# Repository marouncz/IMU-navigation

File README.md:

# IMU-navigation
This is a repository for my bachelor's thesis regarding IMU navigation

# Probrat 13.12.2023
+ mám v pohodě citaci datasheetu?

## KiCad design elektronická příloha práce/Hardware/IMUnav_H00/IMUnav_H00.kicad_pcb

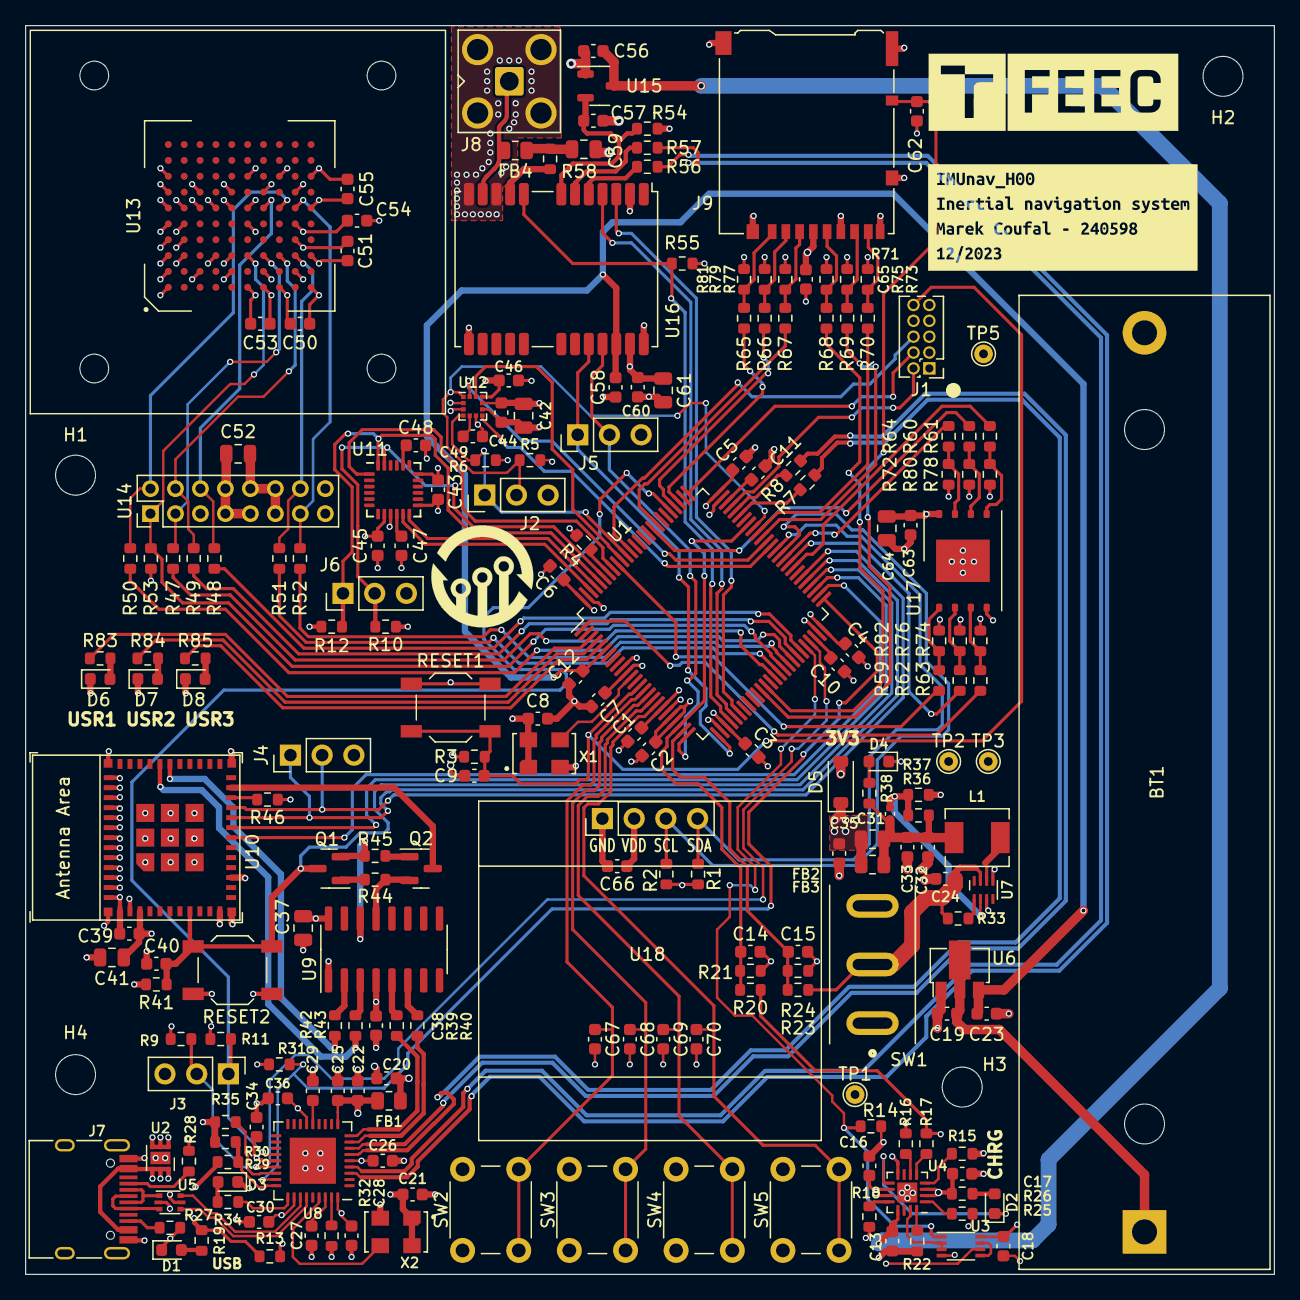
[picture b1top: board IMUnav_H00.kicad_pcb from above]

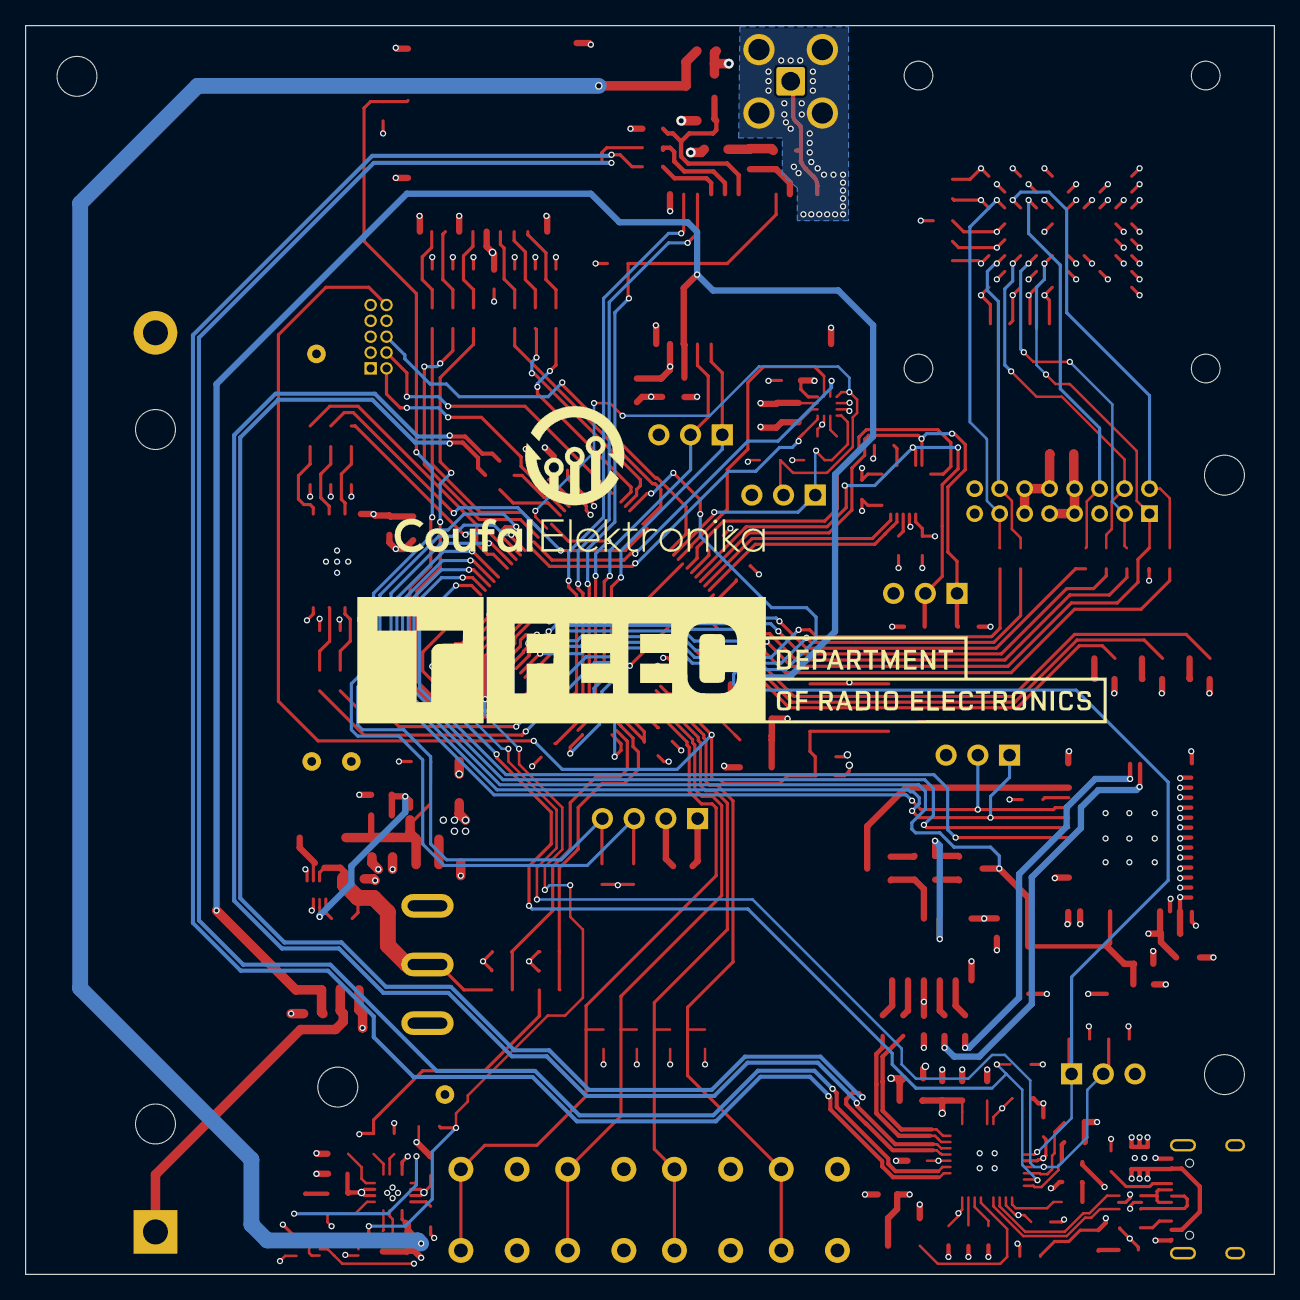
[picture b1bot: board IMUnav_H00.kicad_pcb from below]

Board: 4 copper layers, 100.0 x 100.0 mm, 220 parts (2 on the bottom side), 151 nets.

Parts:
BT1: Li-Ion 18650; BatteryHolder_MPD_BH-18650-PC2
C1, C2, C3, C4, C5, C6, C7, C8, C9, C12, C14, C15, C18, C21, C27, C29, C34, C36, C38, C39, C43, C44, C45, C46, C47, C50, C51, C53, C54, C55, C58, C60, C62, C63, C65, C66, C67, C68, C69, C70: 100n; C_0603_1608Metric
C10, C11: 2u2; C_0603_1608Metric
C13, C19, C23, C40, C56, C57: 1u; C_0603_1608Metric
C16, C17, C20, C22, C24: 4u7; C_0603_1608Metric
C25, C26, C28, C30: 10n; C_0603_1608Metric
C31: 1n; C_0402_1005Metric
C32, C33, C35: 22u; C_0603_1608Metric
C37, C41, C42, C52, C59, C61, C64: 10u; C_0805_2012Metric
C48: 2n2; C_0603_1608Metric
C49: 220n; C_0603_1608Metric
D1, D4: LED_GREEN; LED_0603_1608Metric
D2, D3: LED_RED; LED_0603_1608Metric
D5: B5819W; D_SOD-123
D6, D7, D8: LED_YELLOW; LED_0603_1608Metric
FB1, FB2, FB3, FB4: GZ2012D101TF; R_0805_2012Metric
G1: FEEC_logo
G2: FEEC_logo_long
G3: CoufalElektronika_logo; Coufal_elektronika_notext_10mm
G4: CoufalElektronika_logo; Coufal_elektronika_text_30x13mm
H1, H2, H3, H4: MountingHole; MountingHole_3.2mm_M3
J1: Conn_ARM_JTAG_SWD_10; PinHeader_2x05_P1.27mm_Vertical
J2, J3, J4, J5, J6: Conn_01x03_Pin; PinHeader_1x03_P2.54mm_Vertical
J7: 918-418K2023S40001; USB_C_Receptacle_HRO_TYPE-C-31-M-12
J8: SMA6252A2-3GT50G-50; SMA_Amphenol_901-143_Horizontal
J9: Micro_SD_Card_Det_Hirose_DM3AT; microSD_HC_Hirose_DM3AT-SF-PEJM5
L1: 470n; L_Chilisin_BMRA00040420
Q1, Q2: S8050; SOT-23
R1, R2, R3, R4, R5, R6, R9, R10, R11, R12, R16, R17, R23, R25, R41, R46, R71, R72, R73, R74, R75, R76, R77, R78, R79, R80, R81, R82: 10K; R_0603_1608Metric
R7, R8, R39, R40, R47, R48, R49, R50, R51, R52, R56, R57, R59, R60, R61, R62, R63, R64, R65, R66, R67, R68, R69, R70: 33R; R_0603_1608Metric
R13, R14, R15, R29, R30, R31, R33, R35, R53, R54, R55: 100K; R_0603_1608Metric
R18, R19, R22, R83, R84, R85: 1K8; R_0603_1608Metric
R20: 27K; R_0603_1608Metric
R21: 33K; R_0603_1608Metric
R24: 30K; R_0603_1608Metric
R26: 1K; R_0603_1608Metric
R27, R28: 5K1; R_0603_1608Metric
R32, R44, R45: 12K; R_0603_1608Metric
R34, R38, R42, R43: 470R; R_0603_1608Metric
R36: 68K; R_0603_1608Metric
R37: 15K; R_0603_1608Metric
R58: 10R; R_0603_1608Metric
RESET1, RESET2: SW_SPST; SW_SPST_TL3342
SW1: MT-102; TE_A101SYCQ04
SW2, SW3, SW4, SW5: SW_SPST; SW_PUSH_6mm_H13mm
TP1, TP2, TP3, TP5: TestPoint; TestPoint_THTPad_D1.5mm_Drill0.7mm
U1: STM32F446VETx; LQFP-100_14x14mm_P0.5mm
U2: TVS0500DRV; WSON-6-1EP_2x2mm_P0.65mm_EP1x1.6mm
U3: 74LVC2G02; VSSOP-8_2.3x2mm_P0.5mm
U4: BQ24075RGT; VQFN-16-1EP_3x3mm_P0.5mm_EP1.6x1.6mm
U5: USBLC6-2P6; SOT-666
U6: HT7533-1; SOT-89-3
U7: TPS62823DLC; Texas_VSON-HR-8_1.5x2mm_P0.5mm
U8: USB2514B-AEZC-TR; QFN-36-1EP_6x6mm_P0.5mm_EP3.7x3.7mm
U9: CH340G; SOIC-16_3.9x9.9mm_P1.27mm
U10: ESP32-C3-MINI-1
U11: MPU-6050; InvenSense_QFN-24_4x4mm_P0.5mm
U12: LSM303AGR; LGA-12_2x2mm_P0.5mm
U13: ADIS16505-2BMLZ; BGA-100_10x10_15.0x15.0mm
U14: ADIS16505-x/PCBZ; ADIS16505-PCBZ
U15: XC6206P332MR; SOT-23-3
U16: NEO-M8U; ublox_NEO
U17: XT25F256BWSIGT; WSON-8-1EP_8x6mm_P1.27mm_EP3.4x4.3mm
U18: OLED_I2C; Display_128x64_096_I2C
X1, X2: SX5M24.000M20F30TNN; OSC_ECS-3963-250-BN-TR
kibuzzard-656DA471: G***; kibuzzard-656DA471

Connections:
+3V3: C1.1, C2.1, C3.1, C4.1, C5.1, C6.1, C7.1, C8.1, C20.1, C21.1, C34.1, C35.1, C36.1, C37.1, C38.1, C39.1, C41.1, C42.1, C43.1, C44.1, C45.1, C46.1, C50.1, C51.1, C52.1, C53.1, C54.1, C55.1, C60.1, C61.1, C63.1, C64.1, C65.1, C66.1, D5.1 (K), FB1.1, FB2.2, FB3.2, J1.1 (VTref), J9.4 (VDD), R1.1, R2.1, R3.1, R5.1, R6.1, R9.1, R10.1, R11.1, R12.1, R31.1, R41.1, R46.1, R53.1, R55.1, R71.1, R72.1, R73.1, R74.1, R75.1, R76.1, R77.1, R78.1, R79.1, R80.1, R81.1, R82.1, TP3.1, U1.11 (VDD), U1.19 (VDD), U1.21 (VREF+), U1.22 (VDDA), U1.28 (VDD), U1.50 (VDD), U1.75 (VDD), U1.100 (VDD), U8.15 (VDD33), U8.23 (VDD33), U9.4 (V3), U9.16 (VCC), U10.3 (3V3), U11.8 (VDDIO), U11.13 (VDD), U12.2 (CS_XL), U12.3 (CS_MAG), U12.9 (VDD), U12.10 (VDDIO), U13.C7 (VDD), U13.D6 (VDD), U13.E3 (VDD), U13.G1 (VDD), U13.H1 (VDD), U13.J4 (VDD), U13.J5 (VDD), U13.K6 (VDD), U14.10 (VDD), U14.11 (VDD), U14.12 (VDD), U16.2 (D_SEL), U16.23 (VCC), U17.8 (VCC), U18.2 (VCC), X1.1 (Tri-State), X1.4 (Vcc), X2.1 (Tri-State), X2.4 (Vcc)
+5V: C13.1, C56.1, J7.A4 (VBUS), J7.A9 (VBUS), J7.B4 (VBUS), J7.B9 (VBUS), R13.1, R17.1, R19.1, R20.1, R29.1, U2.4 (IN), U2.5 (IN), U2.6 (IN), U3.6, U4.13 (IN), U5.5 (VBUS), U15.3 (VI)
+BATT: C24.1, R23.1, R33.1, SW1.2 (B), U7.7 (VIN)
/ESP32/ESP_D+: R39.1, U8.9 (USBDP_DN4/PRT_DIS_P4)
/ESP32/ESP_D-: R40.1, U8.8 (USBDM_DN4/PRT_DIS_M4)
/GPS/GPS_BCKP_POWER: C12.1, C23.1, C58.1, U1.6 (VBAT), U6.3 (VOUT), U16.22 (V_BCKP)
/GPS/GPS_D+: R57.1, U8.4 (USBDP_DN2/PRT_DIS_P2)
/GPS/GPS_D-: R56.1, U8.3 (USBDM_DN2/PRT_DIS_M2)
/USB+Power/+3V3USB: C22.1, C25.1, C26.1, C28.1, C30.1, FB1.2, U8.5 (VDDA33), U8.10 (VDDA33), U8.29 (VDDA33), U8.36 (VDDA33)
/USB+Power/D+: U5.4 (I/O2), U8.31 (USBDP_UP)
/USB+Power/D-: U5.6 (I/O1), U8.30 (USBDM_UP)
/USB+Power/USB3_D+: R8.2, U8.7 (USBDP_DN3/PRT_DIS_P3)
/USB+Power/USB3_D-: R7.2, U8.6 (USBDM_DN3/PRT_DIS_M3)
ADIS_DIN: R48.1, U1.45 (PE14)
ADIS_DOUT: R49.1, U1.44 (PE13)
ADIS_DR: R52.1, U1.42 (PE11)
ADIS_SCLK: R50.1, U1.43 (PE12)
ADIS_SYNC: R51.1, U1.40 (PE9)
ADIS_~CS: R47.1, U1.39 (PE8)
ADIS_~RST: R53.2, U1.41 (PE10), U13.F3 (~RST), U14.1 (~RST)
BATT_VOLTAGE: C15.1, R23.2, R24.1, U1.24 (PA1)
BUTTON1: C67.1, SW2.2 (B), U1.15 (PC0)
BUTTON2: C68.1, SW3.2 (B), U1.16 (PC1)
BUTTON3: C69.1, SW4.2 (B), U1.17 (PC2)
BUTTON4: C70.1, SW5.2 (B), U1.18 (PC3)
ESP_CTS1: U1.53 (PB14), U10.19 (GPIO5/ADC2_CH0)
ESP_RST: C40.2, Q1.3 (C), R41.2, RESET2.2 (B), U1.54 (PB15), U10.8 (EN/CHIP_PU)
ESP_RTS1: U1.52 (PB13), U10.18 (GPIO4/ADC1_CH4)
ESP_RX1: J4.1, U1.55 (PD8), U10.20 (GPIO6)
ESP_TX1: J4.2, U1.56 (PD9), U10.21 (GPIO7)
GND: BT1.2 (-), C1.2, C2.2, C3.2, C4.2, C5.2, C6.2, C7.2, C8.2, C9.2, C10.2, C11.2, C12.2, C13.2, C14.2, C15.2, C16.2, C17.2, C18.2, C19.2, C20.2, C21.2, C22.2, C23.2, C24.2, C25.2, C26.2, C27.2, C28.2, C29.2, C30.2, C32.2, C33.2, C34.2, C35.2, C36.2, C37.2, C38.2, C39.2, C40.1, C41.2, C42.2, C43.2, C44.2, C45.2, C46.2, C47.2, C48.2, C49.2, C50.2, C51.2, C52.2, C53.2, C54.2, C55.2, C56.2, C57.2, C58.2, C59.2, C60.2, C61.2, C62.2, C63.2, C64.2, C65.2, C66.2, C67.2, C68.2, C69.2, C70.2, D1.1 (K), D3.1 (K), D4.1 (K), D5.2 (A), D6.1 (K), D7.1 (K), D8.1 (K), J1.3 (GND), J1.5 (GND), J1.9 (GNDDetect), J2.3, J3.3, J4.3, J5.3, J6.3, J7.A1 (GND), J7.A12 (GND), J7.B1 (GND), J7.B12 (GND), J8.2 (Ext), J9.6 (VSS), J9.9 (DET_B), J9.11 (SHIELD), R4.2, R13.2, R14.2, R15.2, R16.2, R18.2, R21.2, R22.2, R24.2, R25.2, R27.2, R28.2, R30.2, R32.2, R35.2, R37.2, R54.2, RESET1.1 (A), RESET2.1 (A), SW2.1 (A), SW3.1 (A), SW4.1 (A), SW5.1 (A), TP2.1, TP5.1, U1.10 (VSS), U1.20 (VSSA), U1.27 (VSS), U1.49 (VSS), U1.74 (VSS), U1.99 (VSS), U2.1 (GND), U2.2 (GND), U2.3 (GND), U2.7 (GND), U3.4 (GND), U4.8 (VSS), U4.17 (VSS), U5.2 (GND), U6.1 (GND), U7.3 (AGND), U7.5 (PGND), U8.37 (VSS), U9.1 (GND), U10.1 (GND), U10.2 (GND), U10.11 (GND), U10.14 (GND), U10.36 (GND), U10.37 (GND), U10.38 (GND), U10.39 (GND), U10.40 (GND), U10.41 (GND), U10.42 (GND), U10.43 (GND), U10.44 (GND), U10.45 (GND), U10.46 (GND), U10.47 (GND), U10.48 (GND), U10.49 (GND), U10.50 (GND), U10.51 (GND), U10.52 (GND), U10.53 (GND), U11.9 (AD0), U11.18 (GND), U12.6 (GND), U12.8 (GND), U13.A1 (GND), U13.A2 (GND), U13.A3 (GND), U13.A4 (GND), U13.A5 (GND), U13.A6 (GND), U13.A7 (GND), U13.A8 (GND), U13.B3 (GND), U13.B4 (GND), U13.B5 (GND), U13.B6 (GND), U13.C2 (GND), U13.C6 (GND), U13.D3 (GND), U13.E2 (GND), U13.E6 (GND), U13.E7 (GND), U13.F1 (GND), U13.F5 (GND), U13.F6 (GND), U13.F8 (GND), U13.G2 (GND), U13.G7 (GND), U13.H8 (GND), U13.J2 (GND), U13.J7 (GND), U13.K1 (GND), U13.K3 (GND), U13.K8 (GND), U14.7 (GND), U14.8 (GND), U14.9 (GND), U15.1 (GND), U16.10 (GND), U16.12 (GND), U16.13 (GND), U16.24 (GND), U17.4 (GND), U17.9 (EP), U18.1 (GND), X1.2 (GND), X2.2 (GND)
GPS_EXTINT: U1.30 (PA5), U16.4 (EXTINT)
GPS_RX: J5.2, U1.25 (PA2), U16.21 (RXD/SPI_MOSI)
GPS_TIMEPULSE: U1.31 (PA6), U16.3 (TIMEPULSE)
GPS_TX: J5.1, U1.26 (PA3), U16.20 (TXD/SPI_MISO)
GPS_~RESET: R55.2, U1.29 (PA4), U16.8 (~RESET)
HUB_SCL: J3.2, R9.2, U1.47 (PB10), U8.24 (SCL/SMBCLK/CFG_SEL0)
HUB_SDA: J3.1, R11.2, U1.80 (PC12), U8.22 (SDA/SMBDATA/NON_REM1)
HUB_~RESET: R31.2, U1.51 (PB12), U8.26 (RESET_N)
LED1: R83.1, U1.3 (PE4)
LED2: R84.1, U1.4 (PE5)
LED3: R85.1, U1.5 (PE6)
LSM_INT1ACCL: U1.64 (PC7), U12.12 (INT_1_XL)
LSM_INT2ACCL: U1.91 (PB5), U12.11 (INT_2_XL)
LSM_INTMAG: U1.63 (PC6), U12.7 (INT_MAG/DRDY)
LSM_SCL: J2.2, R5.2, U1.67 (PA8), U12.1 (SCL/SPC)
LSM_SDA: J2.1, R6.2, U1.90 (PB4), U12.4 (SDA/SDI/SDO)
MPU_CLKIN: U1.93 (PB7), U11.1 (CLKIN)
MPU_FSYNC: U1.98 (PE1), U11.11 (FSYNC)
MPU_INT: U1.97 (PE0), U11.12 (INT)
MPU_SCL: J6.2, R10.2, U1.95 (PB8), U11.23 (SCL)
MPU_SDA: J6.1, R12.2, U1.96 (PB9), U11.24 (SDA)
unnamed: BT1.1 (+), C17.1, C18.1, C19.1, R26.1, U3.8 (VCC), U4.2 (BAT), U4.3 (BAT), U6.2 (VIN)
unnamed: C31.1, C32.1, C33.1, FB2.1, FB3.1, L1.2, R36.2, R38.2
unnamed: C59.1, FB4.1, R58.2
unnamed: D1.2 (A), R19.2
unnamed: D2.2 (A), R26.2
unnamed: D2.1 (K), U4.9 (~CHG)
unnamed: D3.2 (A), R34.2
unnamed: D4.2 (A), R38.1
unnamed: D6.2 (A), R83.2
unnamed: D7.2 (A), R84.2
unnamed: D8.2 (A), R85.2
unnamed: J7.A5 (CC1), R28.1
unnamed: J7.B5 (CC2), R27.1
unnamed: J7.A6 (D+), J7.B6 (D+), U5.3 (I/O2)
unnamed: J7.A7 (D-), J7.B7 (D-), U5.1 (I/O1)
unnamed: FB4.2, J8.1 (In), U16.11 (RF_IN)
unnamed: J9.5 (CLK), R68.2, R75.2
unnamed: J9.3 (CMD), R67.2, R77.2
unnamed: J9.7 (DAT0), R69.2, R73.2
unnamed: J9.8 (DAT1), R70.2, R71.2
unnamed: J9.1 (DAT2), R65.2, R81.2
unnamed: J9.2 (DAT3/CD), R66.2, R79.2
unnamed: Q1.1 (B), R44.1
unnamed: Q1.2 (E), R45.2, U9.14 (~RTS)
unnamed: Q2.1 (B), R45.1
unnamed: Q2.3 (C), U10.23 (GPIO9)
unnamed: Q2.2 (E), R44.2, U9.13 (~DTR)
unnamed: C16.1, SW1.1 (A), TP1.1, U4.10 (OUT), U4.11 (OUT)
unnamed: R4.1, U1.94 (BOOT0)
unnamed: U1.12 (PH0), X1.3 (OUT)
unnamed: C10.1, U1.48 (VCAP_1)
unnamed: C11.1, U1.73 (VCAP_2)
unnamed: U3.5, U3.7
unnamed: R16.1, U4.6 (EN1)
unnamed: R17.2, U4.5 (EN2)
unnamed: R18.1, U4.12 (ILIM)
unnamed: R22.1, U4.16 (ISET)
unnamed: U3.2, U3.3, U4.15 (SYSOFF)
unnamed: R25.1, U4.1 (TS)
unnamed: R15.1, U4.4 (~CE)
unnamed: R33.2, U7.1 (EN)
unnamed: C31.2, R36.1, R37.1, U7.2 (FB)
unnamed: L1.1, U7.6 (SW)
unnamed: C29.1, U8.14 (CRFILT)
unnamed: R35.1, U8.25 (HS_IND/CFG_SEL1)
unnamed: C27.1, U8.34 (PLLFILT)
unnamed: R32.1, U8.35 (RBIAS)
unnamed: R34.1, U8.28 (SUSP_IND/LOCAL_PWR/NON_REM0)
unnamed: R29.2, R30.1, U8.27 (VBUS_DET)
unnamed: U8.33 (XTALIN/CLKIN), X2.3 (OUT)
unnamed: R43.2, U9.3 (RXD)
unnamed: R42.2, U9.2 (TXD)
unnamed: R39.2, U9.5 (UD+)
unnamed: R40.2, U9.6 (UD-)
unnamed: R46.2, U10.22 (GPIO8)
unnamed: R42.1, U10.30 (GPIO20/U0RXD)
unnamed: R43.1, U10.31 (GPIO21/U0TXD)
unnamed: C48.1, U11.20 (CPOUT)
unnamed: C47.1, U11.10 (REGOUT)
unnamed: C49.1, U12.5 (C1)
unnamed: R48.2, U13.G6 (DIN), U14.6 (DIN)
unnamed: R49.2, U13.H3 (DOUT), U14.4 (DOUT)
unnamed: R52.2, U13.J6 (DR), U14.13 (DR)
unnamed: R50.2, U13.H6 (SCLK), U14.2 (SCLK)
unnamed: R51.2, U13.J3 (SYNC), U14.14 (SYNC)
unnamed: R47.2, U13.G3 (~CS), U14.3 (~CS)
unnamed: C57.1, R54.1, U15.2 (VO), U16.7 (VDD_USB)
unnamed: R56.2, U16.5 (USB_DM)
unnamed: R57.2, U16.6 (USB_DP)
unnamed: R58.1, U16.9 (VCC_RF)
unnamed: R60.2, R80.2, U17.6 (SCLK)
unnamed: R61.2, R78.2, U17.5 (SI/SIO0)
unnamed: R62.2, R76.2, U17.2 (SO/SIO1)
unnamed: R59.2, R82.2, U17.1 (~CS)
unnamed: R64.2, R72.2, U17.7 (~HOLD/SIO3)
unnamed: R63.2, R74.2, U17.3 (~WP/SIO2)
OLED_SCL: R2.2, U1.61 (PD14), U18.3 (SCL)
OLED_SDA: R1.2, U1.62 (PD15), U18.4 (SDA)
PWR_OFF: R14.1, U1.46 (PE15), U3.1
QSPI_IO0: R61.1, U1.58 (PD11)
QSPI_IO1: R62.1, U1.59 (PD12)
QSPI_IO2: R63.1, U1.1 (PE2)
QSPI_IO3: R64.1, U1.60 (PD13)
QSPI_SCLK: R60.1, U1.84 (PD3)
QSPI_~CS: R59.1, U1.92 (PB6)
SD_CARDSW: C62.1, J9.10 (DET_A), U1.36 (PB1)
SD_CLK: R68.1, U1.37 (PB2)
SD_CMD: R67.1, U1.83 (PD2)
SD_DAT0: R69.1, U1.65 (PC8)
SD_DAT1: R70.1, U1.66 (PC9)
SD_DAT2: R65.1, U1.78 (PC10)
SD_DAT3: R66.1, U1.79 (PC11)
STM_D+: R8.1, U1.71 (PA12)
STM_D-: R7.1, U1.70 (PA11)
SWD_CLK: J1.4 (SWCLK/TCK), U1.76 (PA14)
SWD_NRST: C9.1, J1.10 (~RESET), R3.2, RESET1.2 (B), U1.14 (NRST)
SWD_SWIO: J1.2 (SWDIO/TMS), U1.72 (PA13)
SWD_SWO: J1.6 (SWO/TDO), U1.89 (PB3)
USB_VOLTAGE: C14.1, R20.2, R21.1, U1.23 (PA0), U1.68 (PA9)

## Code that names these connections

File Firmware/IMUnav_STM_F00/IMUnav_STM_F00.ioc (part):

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Mcu.Name=STM32F446V(C-E)Tx
Mcu.Package=LQFP100
Mcu.UserName=STM32F446VETx
PA0-WKUP.GPIOParameters=GPIO_Label
PA0-WKUP.GPIO_Label=USB_VOLTAGE_ADC
PA0-WKUP.Signal=ADCx_IN0
PA1.GPIOParameters=GPIO_Label
PA1.GPIO_Label=BATT_VOLTAGE
PA1.Signal=ADCx_IN1
PA11.Mode=Device_Only
PA11.Signal=USB_OTG_FS_DM
PA12.Mode=Device_Only
PA12.Signal=USB_OTG_FS_DP
PA13.Mode=Trace_Asynchronous_SW
PA13.Signal=SYS_JTMS-SWDIO
PA14.Mode=Trace_Asynchronous_SW
PA14.Signal=SYS_JTCK-SWCLK
PA2.GPIOParameters=GPIO_Label
PA2.GPIO_Label=GPS_RX
PA2.Mode=Asynchronous
PA2.Signal=USART2_TX
PA3.GPIOParameters=GPIO_Label
PA3.GPIO_Label=GPS_TX
PA3.Mode=Asynchronous
PA3.Signal=USART2_RX
PA4.GPIOParameters=GPIO_Label
PA4.GPIO_Label=GPS_RST
PA4.Signal=GPIO_Output
PA8.GPIOParameters=GPIO_Pu
PA8.GPIO_Pu=GPIO_PULLUP
PA8.Mode=I2C
PA8.Signal=I2C3_SCL
PB1.GPIOParameters=GPIO_PuPd,GPIO_Label
PB1.GPIO_Label=SD_CARDSW
PB1.GPIO_PuPd=GPIO_PULLUP
PB1.Signal=GPIO_Input
PB10.GPIOParameters=GPIO_Label,GPIO_Pu
PB10.GPIO_Label=HUB_SCL
PB10.GPIO_Pu=GPIO_NOPULL
PB10.Mode=I2C
PB10.Signal=I2C2_SCL
PB12.GPIOParameters=GPIO_Label
PB12.GPIO_Label=HUB_RESET
PB12.Signal=GPIO_Output
PB2.Mode=SD_4_bits_Wide_bus
PB2.Signal=SDIO_CK
PB3.Mode=Trace_Asynchronous_SW
PB3.Signal=SYS_JTDO-SWO
PB4.GPIOParameters=GPIO_Pu
PB4.GPIO_Pu=GPIO_PULLUP
PB4.Mode=I2C
PB4.Signal=I2C3_SDA
PB5.GPIOParameters=GPIO_Label
PB5.GPIO_Label=LSM_INT2ACCL
PB5.Signal=GPIO_Input
PB6.Mode=Single Bank 1
PB6.Signal=QUADSPI_BK1_NCS
PB7.GPIOParameters=GPIO_Label
PB7.GPIO_Label=MPU_CLKIN
PB7.Signal=GPIO_Output
PB8.Mode=I2C
PB8.Signal=I2C1_SCL
PB9.Mode=I2C
PB9.Signal=I2C1_SDA
PC0.GPIOParameters=GPIO_PuPd,GPIO_Label
PC0.GPIO_Label=BUTTON1
PC0.GPIO_PuPd=GPIO_PULLUP
PC0.Signal=GPIO_Input
PC1.GPIOParameters=GPIO_PuPd,GPIO_Label
PC1.GPIO_Label=BUTTON2
PC1.GPIO_PuPd=GPIO_PULLUP
PC1.Signal=GPIO_Input
PC10.Mode=SD_4_bits_Wide_bus
PC10.Signal=SDIO_D2
PC11.Mode=SD_4_bits_Wide_bus
PC11.Signal=SDIO_D3
PC12.GPIOParameters=GPIO_Label,GPIO_Pu
PC12.GPIO_Label=HUB_SDA
PC12.GPIO_Pu=GPIO_NOPULL
PC12.Mode=I2C
PC12.Signal=I2C2_SDA
PC14-OSC32_IN.Mode=LSE-External-Oscillator
PC14-OSC32_IN.Signal=RCC_OSC32_IN
PC15-OSC32_OUT.Mode=LSE-External-Oscillator
PC15-OSC32_OUT.Signal=RCC_OSC32_OUT
PC2.GPIOParameters=GPIO_PuPd,GPIO_Label
PC2.GPIO_Label=BUTTON3
PC2.GPIO_PuPd=GPIO_PULLUP
PC2.Signal=GPIO_Input
PC3.GPIOParameters=GPIO_PuPd,GPIO_Label
PC3.GPIO_Label=BUTTON4
PC3.GPIO_PuPd=GPIO_PULLUP
PC3.Signal=GPIO_Input
PC6.GPIOParameters=GPIO_Label
PC6.GPIO_Label=LSM_INTMAG
PC6.Signal=GPXTI6
PC7.GPIOParameters=GPIO_Label
PC7.GPIO_Label=LSM_INT1ACCL
PC7.Signal=GPIO_Input
PC8.Mode=SD_4_bits_Wide_bus
PC8.Signal=SDIO_D0
PC9.Mode=SD_4_bits_Wide_bus
PC9.Signal=SDIO_D1
PD11.Mode=Single Bank 1
PD11.Signal=QUADSPI_BK1_IO0
PD12.Mode=Single Bank 1
PD12.Signal=QUADSPI_BK1_IO1
PD13.Mode=Single Bank 1
PD13.Signal=QUADSPI_BK1_IO3
PD14.GPIOParameters=GPIO_Label
PD14.GPIO_Label=OLED_SCL
PD14.Mode=I2C
PD14.Signal=FMPI2C1_SCL
PD15.GPIOParameters=GPIO_Label
PD15.GPIO_Label=OLED_SDA
PD15.Mode=I2C
PD15.Signal=FMPI2C1_SDA
PD2.Mode=SD_4_bits_Wide_bus
PD2.Signal=SDIO_CMD
PD3.Mode=Single Bank 1
PD3.Signal=QUADSPI_CLK
PE0.GPIOParameters=GPIO_Label
PE0.GPIO_Label=MPU_INT
PE0.Signal=GPXTI0
PE1.GPIOParameters=GPIO_Label
PE1.GPIO_Label=MPU_FSYNC
PE1.Signal=GPIO_Output
PE10.GPIOParameters=GPIO_Label
PE10.GPIO_Label=ADIS_RESET
PE10.Signal=GPIO_Output
PE11.GPIOParameters=GPIO_Label
PE11.GPIO_Label=ADIS_DR
PE11.Signal=GPXTI11
PE12.Mode=Full_Duplex_Master
PE12.Signal=SPI4_SCK
PE13.Mode=Full_Duplex_Master
PE13.Signal=SPI4_MISO
PE14.Mode=Full_Duplex_Master
PE14.Signal=SPI4_MOSI
PE15.GPIOParameters=GPIO_Label
PE15.GPIO_Label=PWR_OFF
PE15.Signal=GPIO_Output
PE2.Mode=Single Bank 1
PE2.Signal=QUADSPI_BK1_IO2
PE4.GPIOParameters=GPIO_Label
PE4.GPIO_Label=LED1
PE4.Signal=GPIO_Output
PE5.GPIOParameters=GPIO_Label
PE5.GPIO_Label=LED2
PE5.Signal=GPIO_Output
PE6.GPIOParameters=GPIO_Label
PE6.GPIO_Label=LED3
PE6.Signal=GPIO_Output
PE8.GPIOParameters=GPIO_Label
PE8.GPIO_Label=ADIS_CS
PE8.Signal=GPIO_Output
PE9.GPIOParameters=GPIO_Label
PE9.GPIO_Label=ADIS_SYNC
PE9.Signal=GPIO_Output
PH0-OSC_IN.Mode=HSE-External-Clock-Source
PH0-OSC_IN.Signal=RCC_OSC_IN
PH1-OSC_OUT.Mode=HSE-External-Clock-Source
PH1-OSC_OUT.Signal=RCC_OSC_OUT
RCC.HSE_VALUE=24000000
RCC.SYSCLKFreq_VALUE=180000000
RCC.SYSCLKSource=RCC_SYSCLKSOURCE_PLLCLK
board=custom

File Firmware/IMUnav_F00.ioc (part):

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Mcu.Name=STM32G474V(B-C-E)Tx
Mcu.Package=LQFP100
Mcu.UserName=STM32G474VETx
PA0.Mode=IN1-Single-Ended
PA0.Signal=ADC1_IN1
PA1.Mode=IN2-Single-Ended
PA1.Signal=ADC1_IN2
PA11.Mode=Device
PA11.Signal=USB_DM
PA12.Mode=Device
PA12.Signal=USB_DP
PA13.Mode=Trace_Asynchronous_SW
PA13.Signal=SYS_JTMS-SWDIO
PA14.Mode=Trace_Asynchronous_SW
PA14.Signal=SYS_JTCK-SWCLK
PA15.Mode=I2C
PA15.Signal=I2C1_SCL
PA5.Mode=Full_Duplex_Master
PA5.Signal=SPI1_SCK
PA6.Mode=Full_Duplex_Master
PA6.Signal=SPI1_MISO
PA7.Mode=Full_Duplex_Master
PA7.Signal=SPI1_MOSI
PA9.Mode=Asynchronous
PA9.Signal=USART1_TX
PB14.Mode=Full_Duplex_Master
PB14.Signal=SPI2_MISO
PB15.Mode=Full_Duplex_Master
PB15.Signal=SPI2_MOSI
PB3.Mode=Trace_Asynchronous_SW
PB3.Signal=SYS_JTDO-SWO
PB7.Mode=I2C
PB7.Signal=I2C1_SDA
PC10.Mode=Asynchronous
PC10.Signal=UART4_TX
PC11.Mode=Asynchronous
PC11.Signal=UART4_RX
PC4.Mode=I2C
PC4.Signal=I2C2_SCL
PC5.Mode=Asynchronous
PC5.Signal=USART1_RX
PC6.Mode=I2C
PC6.Signal=I2C4_SCL
PC7.Mode=I2C
PC7.Signal=I2C4_SDA
PF0-OSC_IN.Mode=I2C
PF0-OSC_IN.Signal=I2C2_SDA
PF9.Mode=Full_Duplex_Master
PF9.Signal=SPI2_SCK
RCC.HSE_VALUE=8000000
RCC.SYSCLKFreq_VALUE=150000000
RCC.SYSCLKSource=RCC_SYSCLKSOURCE_PLLCLK
board=custom

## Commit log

2023-09-27 (agenda) todo file first init
2023-10-02 added experiments with insEKF
2023-10-05 Prubezny commit
2023-10-18 (agenda) updated todo and moved to readme.md
2023-10-25 (agenda) todo list updated, we should record data and try fusing them
2023-10-30 added simultaneous logging functionaliy
2023-10-30 Correct UINT32 manipulation and convertion of gyro and accel data to SI units
2023-10-30 Experiments with insfilterMARG matlab function
2023-11-01 (agenda) todo updated, design decisions, schematic as tasks
2023-11-05 HW design - USB, ESP, DC/DC converter
2023-11-06 Finished USB Hub connection, added battery and power management. Added sheets for IMU and GPS.
2023-11-07 Created symbol for ADIS IMU, added magnetometer
2023-11-08 Added IMU connection, created symbol for ADIS16505 PCB version
2023-11-13 Updated footprints, symbols and 3D models for ADIS165050 BGA and PCB variant
2023-11-13 Added GPS. Changes in power management.
2023-11-14 Changes in power management
2023-11-18 Auto generated STM32CubeIDE files
2023-11-18 Added .gitignore for KiCad file structure
2023-11-19 Finalized and cleaned Power Management, added GPS antenna footprint
2023-11-19 Added uSD card, changed ESP module to C3-MINI, changed MCU to STM32F4
2023-11-19 Added sheets for memory and UserInterface
2023-11-19 Added signal connections to MCU+misc
2023-11-19 Created PCB, configured stackup and DRC
2023-11-21 Changed LSM303C to LSM303AGR
2023-11-22 (agenda) agenda todo list update
2023-11-27 PCB layout - BGA fanout, GPS and USB hub
2023-11-28 USB charger layout
2023-11-30 PCB routing
2023-12-04 Semi-final PCB routing (copper only)
2023-12-04 Silkscreen layout
2023-12-04 PCB touch-ups, bom file for testing
2023-12-06 exported production data
2023-12-14 thesis
2023-12-17 Thesis - IMU/mag
2023-12-17 Thesis, UI, memory
2023-12-18 Thesis - MCU
2023-12-21 Thesis - added appendix
2023-12-21 Thesis - Added Power and ESP
2023-12-21 Thesis - minor text changes, typo fixes
2023-12-21 Thesis - added power consumption table
2023-12-21 Thesis - add HW design
2023-12-22 Created gitignore for Thesis
2023-12-22 Removed ignored files
2023-12-22 removed lock from KiCad file structure
2023-12-25 INS sources
2023-12-26 Thesis - principles of inertial navigation
2023-12-26 Thesis - fixed popletene pojmy bias a drift
2023-12-26 Thesis - fixed minor problems and typos according to email conversation
2023-12-27 Thesis - Fixed citation and references of EGM
2023-12-27 Thesis - added some text and pictures about HW
2023-12-27 Thesis - renamed files to their apparent name
2023-12-27 Added acronyms using acro package
2023-12-27 Thesis - ordered acronyms alphabetically
2023-12-28 Thesis - vytvořený skript pro seřazení citací
2023-12-28 Thesis - added ADIS PCBZ version image
2023-12-28 Thesis - fixed typos
2024-01-01 Thesis - fixed typo
2024-01-02 Thesis - changed \times to \cdot
2024-01-03 Thesis - created presentation
2024-01-03 Thesis - presentation
2024-01-03 Presentation - removed figure and table captions
2024-01-04 Final Semestral thesis commit
2024-01-11 Created new STM32Cube project for F00
2024-01-11 Testing SMBUS
2024-01-12 Firmware - enabled hub over I2C
2024-01-12 Firmware - added OLED and external FLASH
2024-02-06 DMA driver pro adis
2024-02-06 adis EXTI, code cleanup, adis conv and struct
2024-02-08 adis driver updates
2024-02-13 minor SW changes
2024-02-13 fixed casting from adis format to double
2024-02-13 LSM303 driver
2024-02-14 Hardware - upraveny vysky tlacitek a displaye, generovan step
2024-02-18 Testing freertos Qs for data logging
2024-02-20 code touchup
2024-02-20 added HAL code for SDIO and USB
2024-02-27 Ported SDIO with USB MSC
2024-03-09 Working basic with SDIO+FatFS
2024-03-10 Logging data using FatFS to SD in binary
2024-03-10 moved old SW testing
2024-03-10 working python binary decode
2024-03-12 (agenda) updated todo list
2024-03-25 minor fixes
    changed filename to binary, fixed degrees to radians
2024-03-25 changed file names, recorded data
2024-03-26 Matlab tests (not working)
2024-03-26 Inverted Y axis magnetic field (now same as ADIS)
2024-03-26 Testovací data čtverec
2024-04-09 (agenda) todo updated
2024-04-11 Matlab Tests
2024-04-11 gnss draft
2024-04-13 working gps with DMA
2024-04-13 freertos blbosti
2024-04-14 working MPU6050 driver, changed i2c RX callback handeling
2024-04-14 logging all data
2024-04-14 deleted old logs, added new with all sensors
2024-04-14 plotting sample data
2024-04-16 Basic GUI functions
2024-04-16 Generated RTC driver, removed SPI flash code
2024-04-16 Not working sprintf with float
2024-04-17 changed back linker file
2024-04-17 bigger stack size for power task in order to use sprintf with float, calibrated battery sensing
2024-04-17 succesfully printing floats
2024-04-17 configure timer for runtime stats
2024-04-17 Correct RTC prescaler value
2024-04-18 IMU sensitivity calculated by precompiler
2024-04-18 Fixed RTC, using external low speed oscillator
2024-04-18 outline of gui state machine
2024-04-19 GUI state machine
2024-04-19 Optimized stack sizes
2024-04-19 GUI buttons
2024-04-19 Redo SSD1306 library for nonblocking mode using interrupts
2024-04-19 GUI parts
2024-04-20 RTC changes
2024-04-20 Mandatory 3D fix for RTC time sync
2024-04-20 Starting/stopping logger using gui state machine, USB Init/DeInit
2024-04-20 logger gui time
2024-04-21 Matlab generated calibration solver
2024-04-21 calibration procedure draft
2024-04-21 calibration procedures and functions
2024-04-21 Completed calibration functions
2024-04-21 Misc data commit
2024-04-22 countdown for loggin start, usb init at startup
2024-04-24 code refactoring
2024-04-27 Changed to batchelors thesis, new images
2024-05-14 Oživení HW
2024-05-14 Thesis - Firmware
2024-05-14 logged sample data
2024-05-15 Thesis-firmware
2024-05-15 Thesis-Frimware diagrams
2024-05-16 Thesis - finishged FW diagrams
2024-05-19 Thesis - oled task
2024-05-19 Thesis - gui
2024-05-19 Thesis-firmware-fixes, additions
2024-05-20 Thesis - calibration procedure
2024-05-20 thesis-calibration
2024-05-20 Thesis - calibration, csv
2024-05-20 Thesis - padding
2024-05-20 Thesis-created new chapter
2024-05-20 Python and thesis - added zero detection for no data
2024-05-20 matlab experiments
2024-05-21 matlab
2024-05-21 New sample data, Matlab experiments
2024-05-22 Compressed images
2024-05-22 Thesis - update of PDF title and assignment pages
2024-05-22 Thesis-data processing
2024-05-22 Thesis - data processing
2024-05-22 thesis - vliv kalibrace
2024-05-22 Thesis - calibration
2024-05-23 thesis - data fusion
2024-05-23 thesis - laborator
2024-05-23 thesis - labina
2024-05-23 Thesi - tečky u tabulek a obrázků
2024-05-23 thesis - seřazena bibliografie a zkratky
2024-05-23 thesis - minor fixes
2024-05-23 thesis - závěr
2024-05-23 Úvod abstrakt, elektronická příloha
2024-05-25 dirtree elektronické přílohy
2024-05-25 Dirtree edit
2024-05-25 thesis - korektury
2024-06-10 Thesis presentation - removed page with devkits
